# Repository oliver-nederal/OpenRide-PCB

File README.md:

# OpenRide 

A open-source ESP32-based bike computer with GPS tracking and navigation.

## Images

Full 3D assembly
*Coming soon: once enclosure is designed*

PCB 3D Render

PCB

Schematic

Final product
*Coming soon: once finished!*

## Firmware

### https://github.com/oliver-nederal/openride-software (coming soon)

## Features

- Bright resistive 3.2in touchscreen with an auto-brightness sensor
- GNSS positioning (GPS and BeiDou/BDS) precise to 2.5 metres assisted by a built-in compass and barometric altimeter for accurate speed, heading, elevation and gradient calculation.
- MicroSD Card reader for the ability to store offline maps and routes.
- 1S LiPo with switching charger, pass-through power and thermistor-protected charging. Fuel gauge for accurate battery percentage and a charging LED that shows when power is entering the battery.
- 4 firm tactile buttons (2 front, 2 side) which interact with the UI and also as a soft power switch
- USB-C for charging/data/button-free firmware flashing.

## Introduction

Bike computers have been around for half a century now, and for most people who do it as a hobby or a sport. As a prospective cyclist, your main (and only) options are Garmin, Wahoo, and Bryton, which retail for hundreds of dollars and quickly become obsolete when updates end. Moreover, these units are completely glued shut and by design not repairable. As such, I have been motivated to build my own unit which is easily assemblable, fixable, and anyone with a computer can write and update software for.

A lot of inspiration was taken from the bike computers that are on the market right now, and crosses (what in my opinion) is the best of each. 

## Hardware

### Pinout
 
| ESP32-S3 GPIO | Function |
|---|---|
| IO0 | Back button / boot mode |
| IO1 | Power hold (soft power) |
| IO4, IO5 | Up / Down buttons |
| IO6 | Power / OK button |
| IO7 | Display tearing-effect (TE) |
| IO8, IO9 | I2C SDA / SCL (all sensors, touch, fuel gauge) |
| IO10–IO14 | Micro SD (CS, MOSI, CLK, MISO, card detect) |
| IO15 | Accelerometer interrupt |
| IO17, IO18 | GNSS UART (RX, TX) |
| IO19, IO20 | USB D− / D+ |
| IO21 | Buzzer |
| IO38, IO47 | Display WR / DC |
| IO39–IO44, IO2, IO16 | Display data D0–D7 |
| IO48 | Display backlight (PWM) |

## Make it Yourself

The complete list of items required for you is located in the file BOM_consumer.csv

Should you wish to make it yourself, the PCB files are uploaded and the production files are too.  
There are 3 important files:
1. **Open-Ride.zip**: this contains all the Gerber files which tell the PCB manufacturer where to drill, etc...
2. **bom.csv**: Bill-of-Materials containing a list of all the components needed.
3. **positions.csv**:
4. (Optional) **designators.csv**

---

## Contributing
 
Issues/ideas/pull requests are very welcome here, specifically for the hardware.

## License
 
This project is licensed under the MIT License. Please refer to the LICENSE file.

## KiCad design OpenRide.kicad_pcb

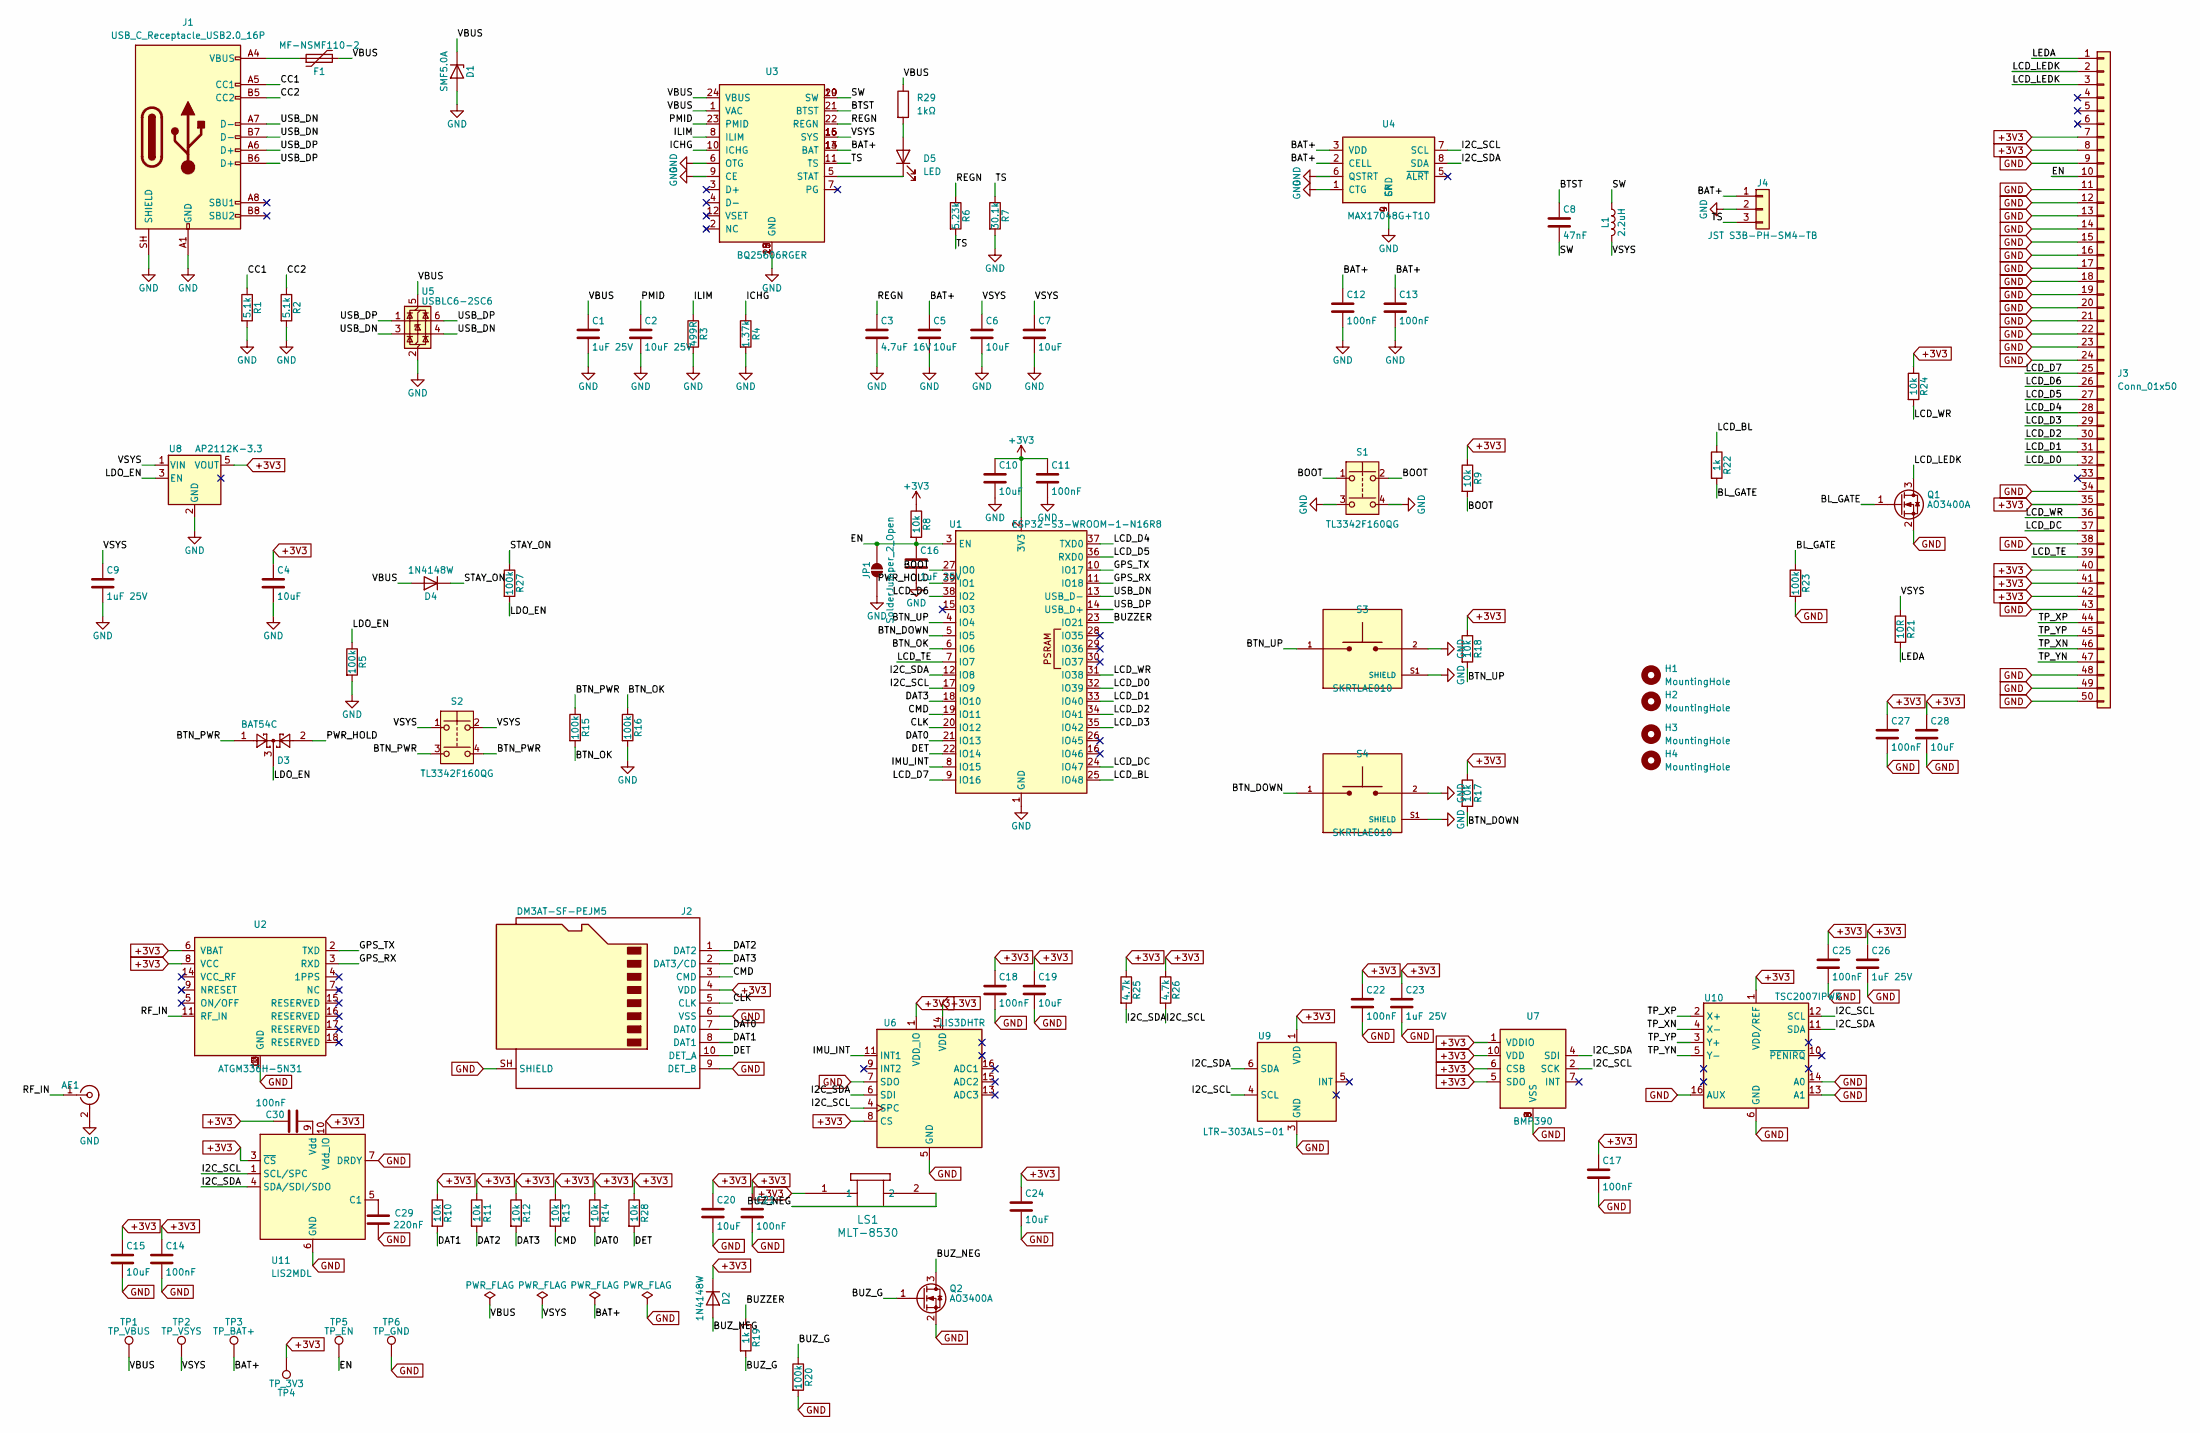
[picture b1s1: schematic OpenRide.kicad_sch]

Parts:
AE1: U.FL; U.FL_Hirose_U.FL-R-SMT-1_Vertical; MPN U.FL-R-SMT-1(10)
C1, C9, C16, C23, C26: 1uF 25V; C_0603_1608Metric; MPN CL10A105KA8NNNC
C2: 10uF 25V; C_0805_2012Metric; MPN CL21A106KAYNNNE
C3: 4.7uF 16V; C_0603_1608Metric; MPN CL10A475KO8NNNC
C4, C5, C6, C7, C10, C15, C19, C20, C24, C28: 10uF; C_0805_2012Metric; MPN CL21A106KAYNNNE
C8: 47nF; C_0603_1608Metric; MPN CL10B473KB8NNNC
C11, C12, C13, C14, C17, C18, C21, C22, C25, C27: 100nF; C_0603_1608Metric; MPN CL10B104KB8NNNC
C29: 220nF; C_0603_1608Metric
C30: 100nF; C_0603_1608Metric
D1: SMF5.0A; D_SOD-123F; MPN SMF5.0A
D2, D4: 1N4148W; D_SOD-123; MPN 1N4148W
D3: BAT54C; SOT-23; MPN BAT54C
D5: LED; LED_Kingbright_APA1606_1.6x0.6mm_Horizontal
F1: MF-NSMF110-2; Fuse_1206_3216Metric; MPN MF-NSMF110-2
H1, H2, H3, H4: MountingHole; MountingHole_2.7mm_M2.5
J1: USB_C_Receptacle_USB2.0_16P; USB_C_Receptacle_HRO_TYPE-C-31-M-12; MPN TYPE-C-31-M-12
J2: DM3AT-SF-PEJM5; microSD_HC_Hirose_DM3AT-SF-PEJM5; MPN DM3AT-SF-PEJM5
J3: Conn_01x50; Hirose_FH12-50S-0.5SH_1x50-1MP_P0.50mm_Horizontal
J4: JST S3B-PH-SM4-TB; JST_PH_S3B-PH-SM4-TB_1x03-1MP_P2.00mm_Horizontal; MPN S3B-PH-SM4-TB(LF)(SN)
JP1: SolderJumper_2_Open; SolderJumper-2_P1.3mm_Open_Pad1.0x1.5mm
L1: 2.2uH; L_Sunlord_SWPA4030S; MPN SWPA4030S2R2MT
LS1: MLT-8530; MLT-8530_JHE
Q1, Q2: AO3400A; SOT-23; MPN AO3400A
R1, R2: 5.1k; R_0603_1608Metric; MPN 0603WAF5101T5E
R3: 499R; R_0603_1608Metric; MPN 0603WAF4990T5E
R4: 1.37k; R_0603_1608Metric; MPN 0603WAF1371T5E
R5, R15, R16, R20, R23, R27: 100k; R_0603_1608Metric; MPN 0603WAF1003T5E
R6: 5.23k; R_0603_1608Metric; MPN 0603WAF5231T5E
R7: 30.1k; R_0603_1608Metric; MPN 0603WAF3012T5E
R8, R9, R10, R11, R12, R13, R14, R17, R18, R24, R28: 10k; R_0603_1608Metric; MPN 0603WAF1002T5E
R19, R22: 1k; R_0603_1608Metric; MPN 0603WAF1001T5E
R21: 10R; R_1206_3216Metric
R25, R26: 4.7k; R_0603_1608Metric; MPN 0603WAF4701T5E
R29: 1kΩ; R_0603_1608Metric
S1, S2: TL3342F160QG; SW_SPST_TL3342; MPN TL3342F160QG
S3, S4: SKRTLAE010; SW_SKRTLAE010; MPN SKRTLAE010
TP1: TP_VBUS; TestPoint_Pad_D1.0mm
TP2: TP_VSYS; TestPoint_Pad_D1.0mm
TP3: TP_BAT+; TestPoint_Pad_D1.0mm
TP4: TP_3V3; TestPoint_Pad_D1.0mm
TP5: TP_EN; TestPoint_Pad_D1.0mm
TP6: TP_GND; TestPoint_Pad_D1.0mm
U1: ESP32-S3-WROOM-1-N16R8; ESP32-S3-WROOM-1; MPN ESP32-S3-WROOM-1-N16R8
U2: ATGM336H-5N31; GPSM-SMD_ATGM336H-TR; MPN ATGM336H-5N31
U3: BQ25606RGER; QFN50P400X400X100-25N; MPN BQ25606RGER
U4: MAX17048G+T10; SON50P200X200X80-9N; MPN MAX17048G+T10
U5: USBLC6-2SC6; SOT-23-6; MPN USBLC6-2SC6
U6: LIS3DHTR; LGA-16_3x3mm_P0.5mm_LayoutBorder3x5y; MPN LIS3DHTR
U7: BMP390; LGA-10_L2.0-W2.0-P0.50-BL; MPN BMP390; LCSC C5124834
U8: AP2112K-3.3; SOT-23-5; MPN AP2112K-3.3TRG1
U9: LTR-303ALS-01; Lite-On_LTR-303ALS-01; MPN LTR-303ALS-01
U10: TSC2007IPWR; TSSOP-16_4.4x5mm_P0.65mm; MPN TSC2007IPWR
U11: LIS2MDL; LGA-12_2x2mm_P0.5mm

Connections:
+3V3: C4.1, C10.1, C11.1, C14.1, C15.1, C17.1, C18.1, C19.1, C20.1, C21.1, C22.1, C23.1, C24.1, C25.1, C26.1, C27.1, C28.1, C30.2, D2.1 (K), J2.4 (VDD), J3.7, J3.8, J3.35, J3.40, J3.41, J3.42, LS1.1, R8.1, R9.1, R10.1, R11.1, R12.1, R13.1, R14.1, R17.1, R18.1, R24.1, R25.1, R26.1, R28.1, TP4.1 (1_1), U1.2 (3V3), U2.6 (VBAT), U2.8 (VCC), U6.1 (VDD_IO), U6.8 (CS), U6.14 (VDD), U7.1 (VDDIO), U7.5 (SDO), U7.6 (CSB), U7.10 (VDD), U8.5 (VOUT), U9.1 (VDD), U10.1 (VDD/REF), U11.3 (~CS), U11.10 (Vdd_IO)
/BAT+: C5.1, C12.1, C13.1, J4.1, TP3.1 (1_1), U3.13 (BAT), U3.14 (BAT), U4.2 (CELL), U4.3 (VDD)
/BL_GATE: Q1.1 (G), R22.2, R23.1
/BOOT: R9.2, S1.1, S1.2, U1.27 (IO0)
/BTN_DOWN: R17.2, S4.1, S4.3, U1.5 (IO5)
/BTN_OK: R15.2, R16.1, U1.6 (IO6)
/BTN_PWR: D3.1, R15.1, S2.3, S2.4
/BTN_UP: R18.2, S3.1, S3.3, U1.4 (IO4)
/BTST: C8.1, U3.21 (BTST)
/BUZZER: R19.1, U1.23 (IO21)
/BUZ_G: Q2.1 (G), R19.2, R20.1
/BUZ_NEG: D2.2 (A), LS1.2, Q2.3 (D)
/CC1: J1.A5 (CC1), R1.1
/CC2: J1.B5 (CC2), R2.1
/CLK: J2.5 (CLK), U1.20 (IO12)
/CMD: J2.3 (CMD), R13.2, U1.19 (IO11)
/DAT0: J2.7 (DAT0), R14.2, U1.21 (IO13)
/DAT1: J2.8 (DAT1), R10.2
/DAT2: J2.1 (DAT2), R11.2
/DAT3: J2.2 (DAT3/CD), R12.2, U1.18 (IO10)
/DET: J2.10 (DET_A), R28.2, U1.22 (IO14)
/EN: C16.1, J3.10, JP1.2 (B), R8.2, TP5.1 (1_1), U1.3 (EN)
/GPS_RX: U1.11 (IO18), U2.3 (RXD)
/GPS_TX: U1.10 (IO17), U2.2 (TXD)
/I2C_SCL: R26.2, U1.17 (IO9), U4.7 (SCL), U6.4 (SPC), U7.2 (SCK), U9.4 (SCL), U10.12 (SCL), U11.1 (SCL/SPC)
/I2C_SDA: R25.2, U1.12 (IO8), U4.8 (SDA), U6.6 (SDI), U7.4 (SDI), U9.6 (SDA), U10.11 (SDA), U11.4 (SDA/SDI/SDO)
/ICHG: R4.1, U3.10 (ICHG)
/ILIM: R3.1, U3.8 (ILIM)
/IMU_INT: U1.8 (IO15), U6.11 (INT1)
/LCD_BL: R22.1, U1.25 (IO48)
/LCD_D0: J3.32, U1.32 (IO39)
/LCD_D1: J3.31, U1.33 (IO40)
/LCD_D2: J3.30, U1.34 (IO41)
/LCD_D3: J3.29, U1.35 (IO42)
/LCD_D4: J3.28, U1.37 (TXD0)
/LCD_D5: J3.27, U1.36 (RXD0)
/LCD_D6: J3.26, U1.38 (IO2)
/LCD_D7: J3.25, U1.9 (IO16)
/LCD_DC: J3.37, U1.24 (IO47)
/LCD_LEDK: J3.2, J3.3, Q1.3 (D)
/LCD_TE: J3.39, U1.7 (IO7)
/LCD_WR: J3.36, R24.2, U1.31 (IO38)
/LDO_EN: D3.3, R5.1, R27.2, U8.3 (EN)
/LEDA: J3.1, R21.2
/PMID: C2.1, U3.23 (PMID)
/PWR_HOLD: D3.2, U1.39 (IO1)
/REGN: C3.1, R6.1, U3.22 (REGN)
/RF_IN: AE1.1 (In), U2.11 (RF_IN)
/STAY_ON: D4.1 (K), R27.1
/SW: C8.2, L1.1, U3.19 (SW), U3.20 (SW)
/TP_XN: J3.46, U10.4 (X-)
/TP_XP: J3.44, U10.2 (X+)
/TP_YN: J3.47, U10.5 (Y-)
/TP_YP: J3.45, U10.3 (Y+)
/TS: J4.3, R6.2, R7.1, U3.11 (TS)
/USB_DN: J1.A7 (D-), J1.B7 (D-), U1.13 (USB_D-), U5.3 (I/O2), U5.4 (I/O2)
/USB_DP: J1.A6 (D+), J1.B6 (D+), U1.14 (USB_D+), U5.1 (I/O1), U5.6 (I/O1)
/VBUS: C1.1, D1.1 (K), D4.2 (A), F1.2, R29.1, TP1.1 (1_1), U3.1 (VAC), U3.24 (VBUS), U5.5 (VBUS)
/VSYS: C6.1, C7.1, C9.1, L1.2, R21.1, S2.1, S2.2, TP2.1 (1_1), U3.15 (SYS), U3.16 (SYS), U8.1 (VIN)
GND: AE1.2 (Ext), C1.2, C2.2, C3.2, C4.2, C5.2, C6.2, C7.2, C9.2, C10.2, C11.2, C12.2, C13.2, C14.2, C15.2, C16.2, C17.2, C18.2, C19.2, C20.2, C21.2, C22.2, C23.2, C24.2, C25.2, C26.2, C27.2, C28.2, C29.2, D1.2 (A), J1.A1 (GND), J1.A12 (GND), J1.B1 (GND), J1.B12 (GND), J1.SH (SHIELD), J2.6 (VSS), J2.9 (DET_B), J2.SH (SHIELD), J3.9, J3.11, J3.12, J3.13, J3.14, J3.15, J3.16, J3.17, J3.18, J3.19, J3.20, J3.21, J3.22, J3.23, J3.24, J3.34, J3.38, J3.43, J3.48, J3.49, J3.50, J4.2, JP1.1 (A), Q1.2 (S), Q2.2 (S), R1.2, R2.2, R3.2, R4.2, R5.2, R7.2, R16.2, R20.2, R23.2, S1.3, S1.4, S3.2, S3.S1 (SHIELD), S3.S2 (SHIELD), S4.2, S4.S1 (SHIELD), S4.S2 (SHIELD), TP6.1 (1_1), U1.1 (GND), U1.40 (GND), U1.41 (GND), U2.1 (GND), U2.10 (GND), U2.12 (GND), U2.13 (GND), U3.6 (OTG), U3.9 (CE), U3.17 (GND), U3.18 (GND), U3.25 (GND), U4.1 (CTG), U4.4 (GND), U4.6 (QSTRT), U4.9 (EP), U5.2 (GND), U6.5 (GND), U6.7 (SDO), U6.10 (GND), U6.12 (GND), U7.3 (VSS), U7.8 (VSS), U7.9 (VSS), U8.2 (GND), U9.3 (GND), U10.6 (GND), U10.13 (A1), U10.14 (A0), U10.16 (AUX), U11.6 (GND), U11.7 (DRDY), U11.8 (GND)
unnamed: D5.2 (A), R29.2
unnamed: D5.1 (K), U3.5 (STAT)
unnamed: F1.1, J1.A4 (VBUS), J1.A9 (VBUS), J1.B4 (VBUS), J1.B9 (VBUS)
unnamed: C29.1, U11.5 (C1)
unnamed: C30.1, U11.9 (Vdd)

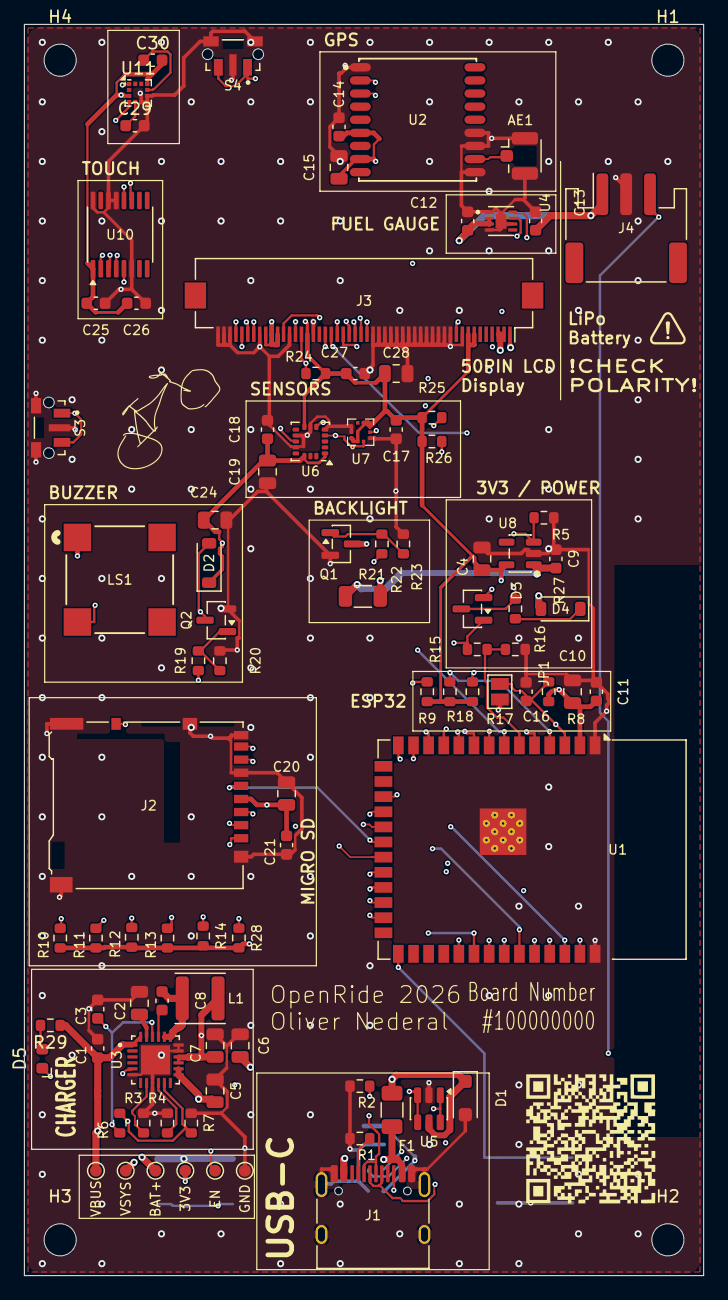
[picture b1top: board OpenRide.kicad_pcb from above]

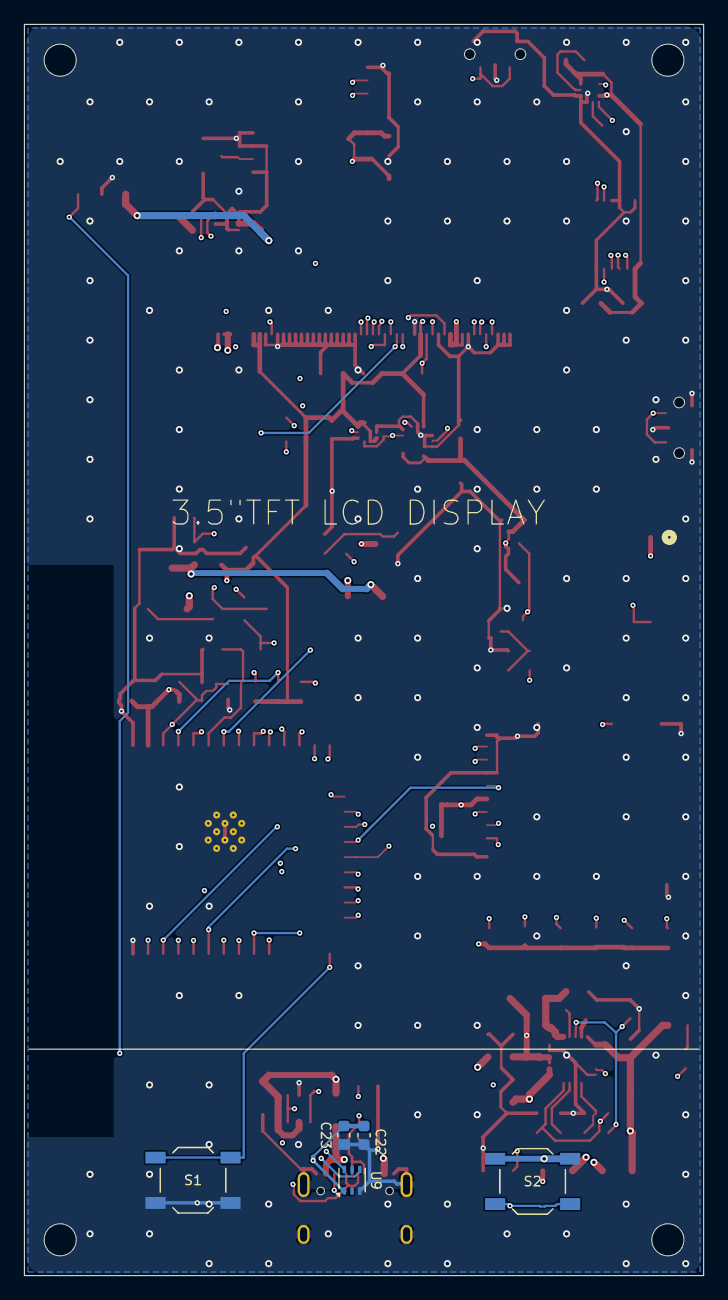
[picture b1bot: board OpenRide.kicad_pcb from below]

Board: 4 copper layers, 57.0 x 105.0 mm, 100 parts (5 on the bottom side), 65 nets.

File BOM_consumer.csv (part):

Designators,Part Name,Source,LCSC Part #,Description,Quantity,Each Price,Total Price,Link
NOTE,,,,! This price is for 2 boards (minimum PCBA quantity at JLCPCB) !,,,,
(N/A) PCB,JLCPCB PCB Service (PCB),JLCPCB,N/A,$25 (Engineering Fee) + $4.60 (Board) (PCB order),1,$29.60,$29.60,https://jlcpcb.com
(N/A) PCB_ASSEMBLY,JLCPCB PCB Assembly Service (PCB-A),JLCPCB,N/A,$51.50 + $16.54 + $2.58 + $60.54 + $6.60 + $0.50 (PCB Assembly option on the PCB order),1,$138.26,$138.26,https://jlcpcb.com
(N/A) 3D-P FILAMENT,Generic PETG,OWN,N/A,Material for the outside casing (Any filament supplier),75g,$0.0200/g,$1.50,
(N/A) 3D-P FILAMENT,Generic TPU95,OWN,N/A,Material for the buttons and USB-C cover (Any filament supplier),10g,$0.0400/g,$0.40,
(N/A) BATTERY,2000mAH 3.7V Li-Po Battery,Adafruit,N/A,1S LiPo battery (use one with a 10k NTC lead),1,$12.50,$12.5,https://www.adafruit.com/product/2011
(N/A) DISPLAY,"3.5"" 320x480px IPS TFT LCD (w/ Resistive Touch)",BuyDisplay,N/A,Display panel with touch,1,$10.87,$10.87,https://www.buydisplay.com/3-5-inch-ips-320x480-tft-lcd-disp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
AE1,Connector Receptacle,JLCPCB,U.FL-R-SMT-1(10),Antenna for GPS (included in JLCPCB PCBA),5,$0.2289,$1.1445,https://jlcpcb.com/parts/componentSearch?searchTxt=U.FL-R-SM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
"C1, C16, C26, C9, C23",Capacitors (1uF 25V),JLCPCB,CL10A105KA8NNNC,Capacitors (included in JLCPCB PCBA),40,$0.0083,$0.3320,https://jlcpcb.com/parts/componentSearch?searchTxt=CL10A105KA8NNNC
"C10, C15, C19, C20, C24, C28, C4, C5, C6, C7, C2",Capacitors (10uF),JLCPCB,CL21A106KAYNNNE,Capacitors (included in JLCPCB PCBA),32,$0.0311,$0.9952,https://jlcpcb.com/parts/componentSearch?searchTxt=CL21A106KAYNNNE
"C11, C12, C13, C14, C17, C18, C21, C25, C27, C22",Capacitors (100nF),JLCPCB,CL10B104KB8NNNC,Capacitors (included in JLCPCB PCBA),53,$0.0104,$0.5512,https://jlcpcb.com/parts/componentSearch?searchTxt=CL10B104KB8NNNC
C3,Capacitor (4.7uF 16V),JLCPCB,CL10A475KO8NNNC,Capacitors (included in JLCPCB PCBA),20,$0.0150,$0.3000,https://jlcpcb.com/parts/componentSearch?searchTxt=CL10A475KO8NNNC
C8,Capacitor (4.7nF),JLCPCB,CL10B473KB8NNNC,Capacitors (included in JLCPCB PCBA),20,$0.0056,$0.1120,https://jlcpcb.com/parts/componentSearch?searchTxt=CL10B473KB8NNNC
D1,TVS Diode,JLCPCB,SMF5.0A,Protects from high-voltage spikes (included in JLCPCB PCBA),15,$0.0284,$0.4260,https://jlcpcb.com/parts/componentSearch?searchTxt=SMF5.0A
"D2, D4",Switching Diode,JLCPCB,1N4148W,Makes current flow in only one direction (included in JLCPCB PCBA),18,$0.0124,$0.2232,https://jlcpcb.com/parts/componentSearch?searchTxt=1N4148W
D3,Schottky Barrier Diode,JLCPCB,BAT54C,To prevent reversed polarity damage (included in JLCPCB PCBA),10,$0.0167,$0.1670,https://jlcpcb.com/parts/componentSearch?searchTxt=BAT54C
F1,Resettable Fuse,JLCPCB,MF-NSMF110-2,Resettable fuse to prevent hardware damage (included in JLCPCB PCBA),6,$0.0372,$0.2232,https://jlcpcb.com/parts/componentSearch?searchTxt=MF-NSMF110-2
J1,USB_C Receptacle,JLCPCB,TYPE-C-31-M-12,USB-C connector for data/charging (included in JLCPCB PCBA),2,$0.1869,$0.3738,https://jlcpcb.com/parts/componentSearch?searchTxt=TYPE-C-31-M-12
J2,MicroSD Card Reader,JLCPCB,DM3AT-SF-PEJM5,Micro-SD card reader for maps/ride recording (included in JLCPCB PCBA),2,$1.39,$2.7816,https://jlcpcb.com/parts/componentSearch?searchTxt=DM3AT-SF-PEJM5
J3,50Pin Bottom Contact SMD Connector,JLCPCB,FH12-50S-0.5SH(55),50-Pin display connector with push lock (included in JLCPCB PCBA),2,$0.8606,$1.7212,https://jlcpcb.com/parts/componentSearch?searchTxt=FH12-50S-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
J4,3Pin SMD Connector,JLCPCB,S3B-PH-SM4-TB(LF)(SN),3-Pin battery connector with click-in (included in JLCPCB PCBA),2,$0.2641,$0.5282,https://jlcpcb.com/parts/componentSearch?searchTxt=S3B-PH-SM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
L1,Inductor (2.2uH),JLCPCB,SWPA4030S2R2MT,Inductor (included in JLCPCB PCBA),6,$0.0532,$0.3192,https://jlcpcb.com/parts/componentSearch?searchTxt=SWPA4030S2R2MT
LS1,Electro-Magnetic Buzzer,JLCPCB,MLT-8530,Buzzer for making sound (included in JLCPCB PCBA),2,$0.1969,$0.3938,https://jlcpcb.com/parts/componentSearch?searchTxt=MLT-8530
"Q1, Q2",30V N-Channel MOSFET,JLCPCB,AO3400A,Turns low current to high current (included in JLCPCB PCBA),8,$0.0789,$0.6312,https://jlcpcb.com/parts/componentSearch?searchTxt=AO3400A
"R1, R2",Resistors (5.1k),JLCPCB,0603WAF5101T5E,Resistors (included in JLCPCB PCBA),20,$0.0015,$0.0300,https://jlcpcb.com/parts/componentSearch?searchTxt=0603WAF5101T5E
"R10, R11, R12, R13, R14, R17, R18, R24, R28, R8, R9",Resistors (10k),JLCPCB,0603WAF1002T5E,Resistors (included in JLCPCB PCBA),32,$0.0020,$0.0640,https://jlcpcb.com/parts/componentSearch?searchTxt=0603WAF1002T5E
"R15, R16, R20, R23, R27, R5",Resistors (100k),JLCPCB,0603WAF1003T5E,Resistors (included in JLCPCB PCBA),22,$0.0029,$0.0638,https://jlcpcb.com/parts/componentSearch?searchTxt=0603WAF1003T5E
"R19, R22",Resistors (1k),JLCPCB,0603WAF1001T5E,Resistors (included in JLCPCB PCBA),20,$0.0017,$0.0340,https://jlcpcb.com/parts/componentSearch?searchTxt=0603WAF1001T5E
R21,Resistors (10R),JLCPCB,1206W4F100JT5E,Resistors (included in JLCPCB PCBA),15,$0.0061,$0.0915,https://jlcpcb.com/parts/componentSearch?searchTxt=1206W4F100JT5E
"R25, R26",Resistors (4.7k),JLCPCB,0603WAF4701T5E,Resistors (included in JLCPCB PCBA),20,$0.0028,$0.0560,https://jlcpcb.com/parts/componentSearch?searchTxt=0603WAF4701T5E
R3,Resistors (499R),JLCPCB,0603WAF4990T5E,Resistors (included in JLCPCB PCBA),20,$0.0015,$0.0300,https://jlcpcb.com/parts/componentSearch?searchTxt=0603WAF4990T5E
R4,Resistors (1.37k),JLCPCB,0603WAF1371T5E,Resistors (included in JLCPCB PCBA),20,$0.0015,$0.0300,https://jlcpcb.com/parts/componentSearch?searchTxt=0603WAF1371T5E
R6,Resistors (5.23k),JLCPCB,0603WAF5231T5E,Resistors (included in JLCPCB PCBA),20,$0.0020,$0.0400,https://jlcpcb.com/parts/componentSearch?searchTxt=0603WAF5231T5E
R7,Resistors (30.1k),JLCPCB,0603WAF3012T5E,Resistors (included in JLCPCB PCBA),20,$0.0016,$0.0320,https://jlcpcb.com/parts/componentSearch?searchTxt=0603WAF3012T5E
"S1, S2",Gull Wing Round Button,JLCPCB,TL3342F160QG,The buttons on top of the bike computer (included in JLCPCB PCBA),4,$0.9375,$3.7500,https://jlcpcb.com/parts/componentSearch?searchTxt=TL3342F160QG
"S3, S4",Round Button SMD(SMT) Tab,JLCPCB,SKRTLAE010,The buttons on the side of the bike computer (included in JLCPCB PCBA),7,$0.1435,$1.0045,https://jlcpcb.com/parts/componentSearch?searchTxt=SKRTLAE010
U1,ESP32-S3-WROOM,JLCPCB,ESP32-S3-WROOM-1-N16R8,The microcontroller (included in JLCPCB PCBA),2,$5.35,$10.6970,https://jlcpcb.com/parts/componentSearch?searchTxt=ESP32-S3-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
U10,Resistive Touchscreen Controller,JLCPCB,TSC2007IPWR,Controller that interprets touchscreen input (included in JLCPCB PCBA),2,$1.38,$2.7618,https://jlcpcb.com/parts/componentSearch?searchTxt=TSC2007IPWR
U2,GPS Module,JLCPCB,ATGM336H-5N31,GPS positioning across the main 2 networks (included in JLCPCB PCBA),2,$3.26,$6.5118,https://jlcpcb.com/parts/componentSearch?searchTxt=ATGM336H-5N31
U3,Lithium Battery Charger,JLCPCB,BQ25606RGER,Synchronous switch-mode buck charger (included in JLCPCB PCBA),2,$1.77,$3.5342,https://jlcpcb.com/parts/componentSearch?searchTxt=BQ25606RGER
U4,Battery Fuel Gauge,JLCPCB,MAX17048G+T10,Chip to see battery charge level (included in JLCPCB PCBA),2,$1.94,$3.8876,https://jlcpcb.com/parts/componentSearch?searchTxt=MAX17048G%2BT10
U5,Transient Voltage Suppressor Diode Array,JLCPCB,USBLC6-2SC6,Protects the data line (included in JLCPCB PCBA),6,$0.0478,$0.2868,https://jlcpcb.com/parts/componentSearch?searchTxt=USBLC6-2SC6
U6,Accelerometer,JLCPCB,LIS3DHTR,"Accelerometer, measures acceleration (included in JLCPCB PCBA)",2,$1.81,$3.6160,https://jlcpcb.com/parts/componentSearch?searchTxt=LIS3DHTR
U7,Barometer,JLCPCB,BMP388,Atmospheric pressure sensor (for height) (included in JLCPCB PCBA),2,$6.83,$13.6618,https://jlcpcb.com/parts/componentSearch?searchTxt=BMP388
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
